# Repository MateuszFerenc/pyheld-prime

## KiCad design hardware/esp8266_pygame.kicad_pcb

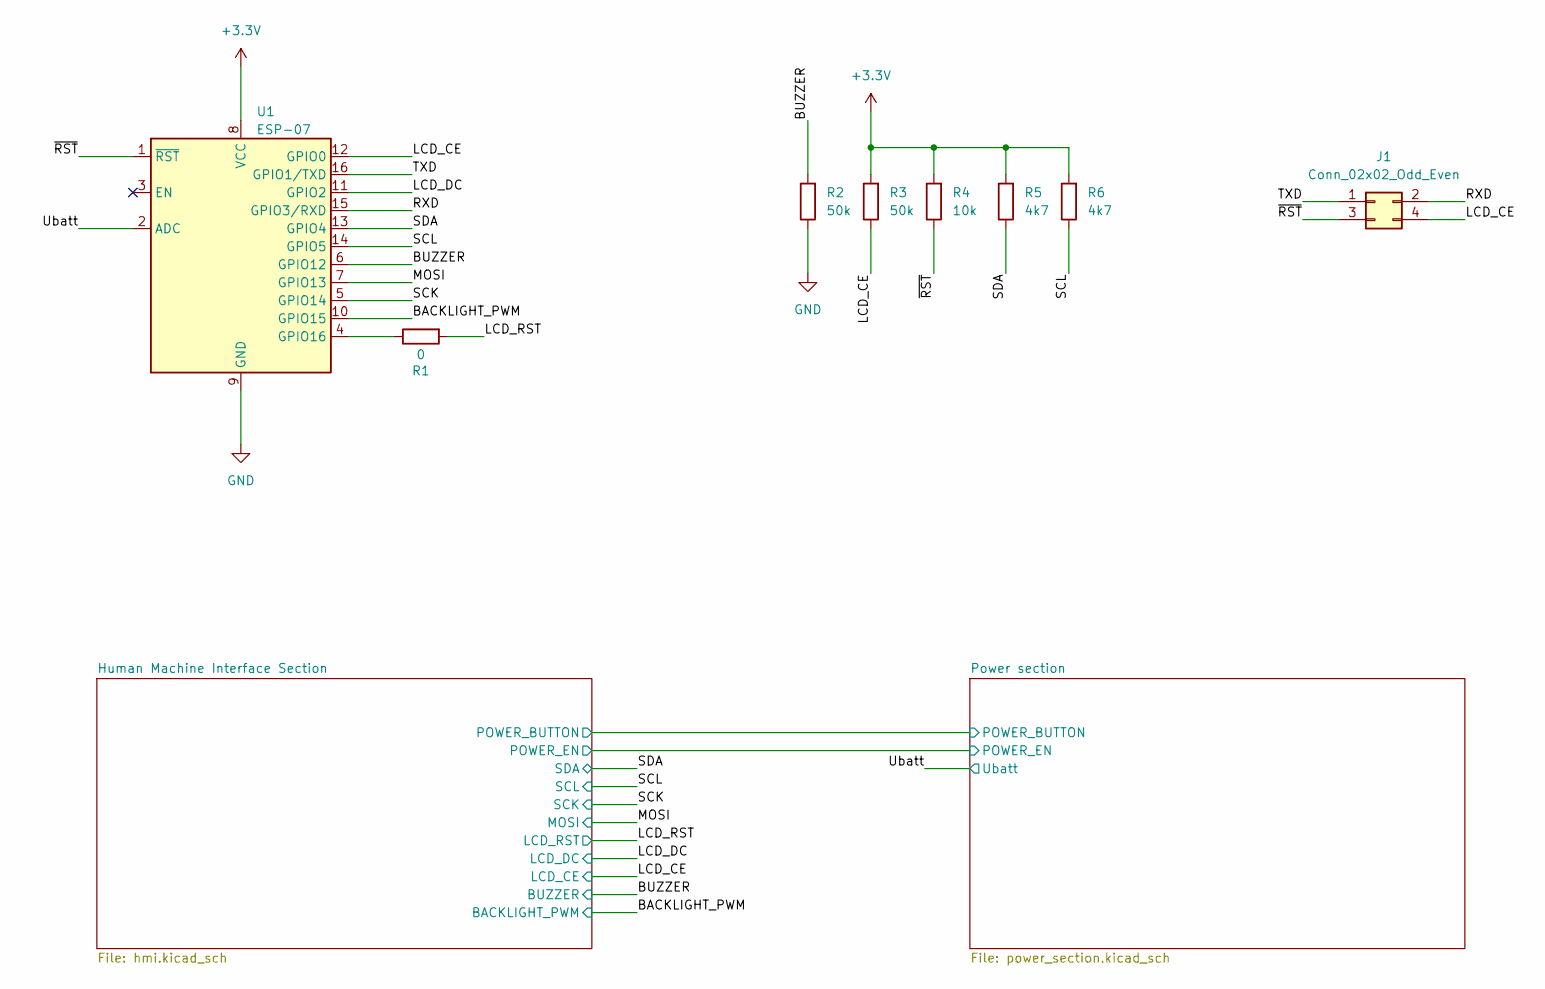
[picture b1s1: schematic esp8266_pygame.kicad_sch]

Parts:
J1: Conn_02x02_Odd_Even; PinHeader_2x02_P2.54mm_Vertical
R1: 0; R_0603_1608Metric
R2, R3: 50k; R_0603_1608Metric
R4: 10k; R_0603_1608Metric
R5, R6: 4k7; R_0603_1608Metric
U1: ESP-07

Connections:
+3.3V: R3.2, R4.2, R5.2, R6.2, U1.8 (VCC); also elsewhere on the board
/BACKLIGHT_PWM: U1.10 (GPIO15); also elsewhere on the board
/BUZZER: R2.2, U1.6 (GPIO12); also elsewhere on the board
/LCD_CE: J1.4, R3.1, U1.12 (GPIO0); also elsewhere on the board
/LCD_DC: U1.11 (GPIO2); also elsewhere on the board
/LCD_RST: R1.2; also elsewhere on the board
/MOSI: U1.7 (GPIO13); also elsewhere on the board
/RXD: J1.2, U1.15 (GPIO3/RXD)
/SCK: U1.5 (GPIO14); also elsewhere on the board
/SCL: R6.1, U1.14 (GPIO5); also elsewhere on the board
/SDA: R5.1, U1.13 (GPIO4); also elsewhere on the board
/TXD: J1.1, U1.16 (GPIO1/TXD)
/Ubatt: U1.2 (ADC); also elsewhere on the board
/~RST: J1.3, R4.1, U1.1 (~RST)
GND: R2.1, U1.9 (GND); also elsewhere on the board
unnamed: R1.1, U1.4 (GPIO16)

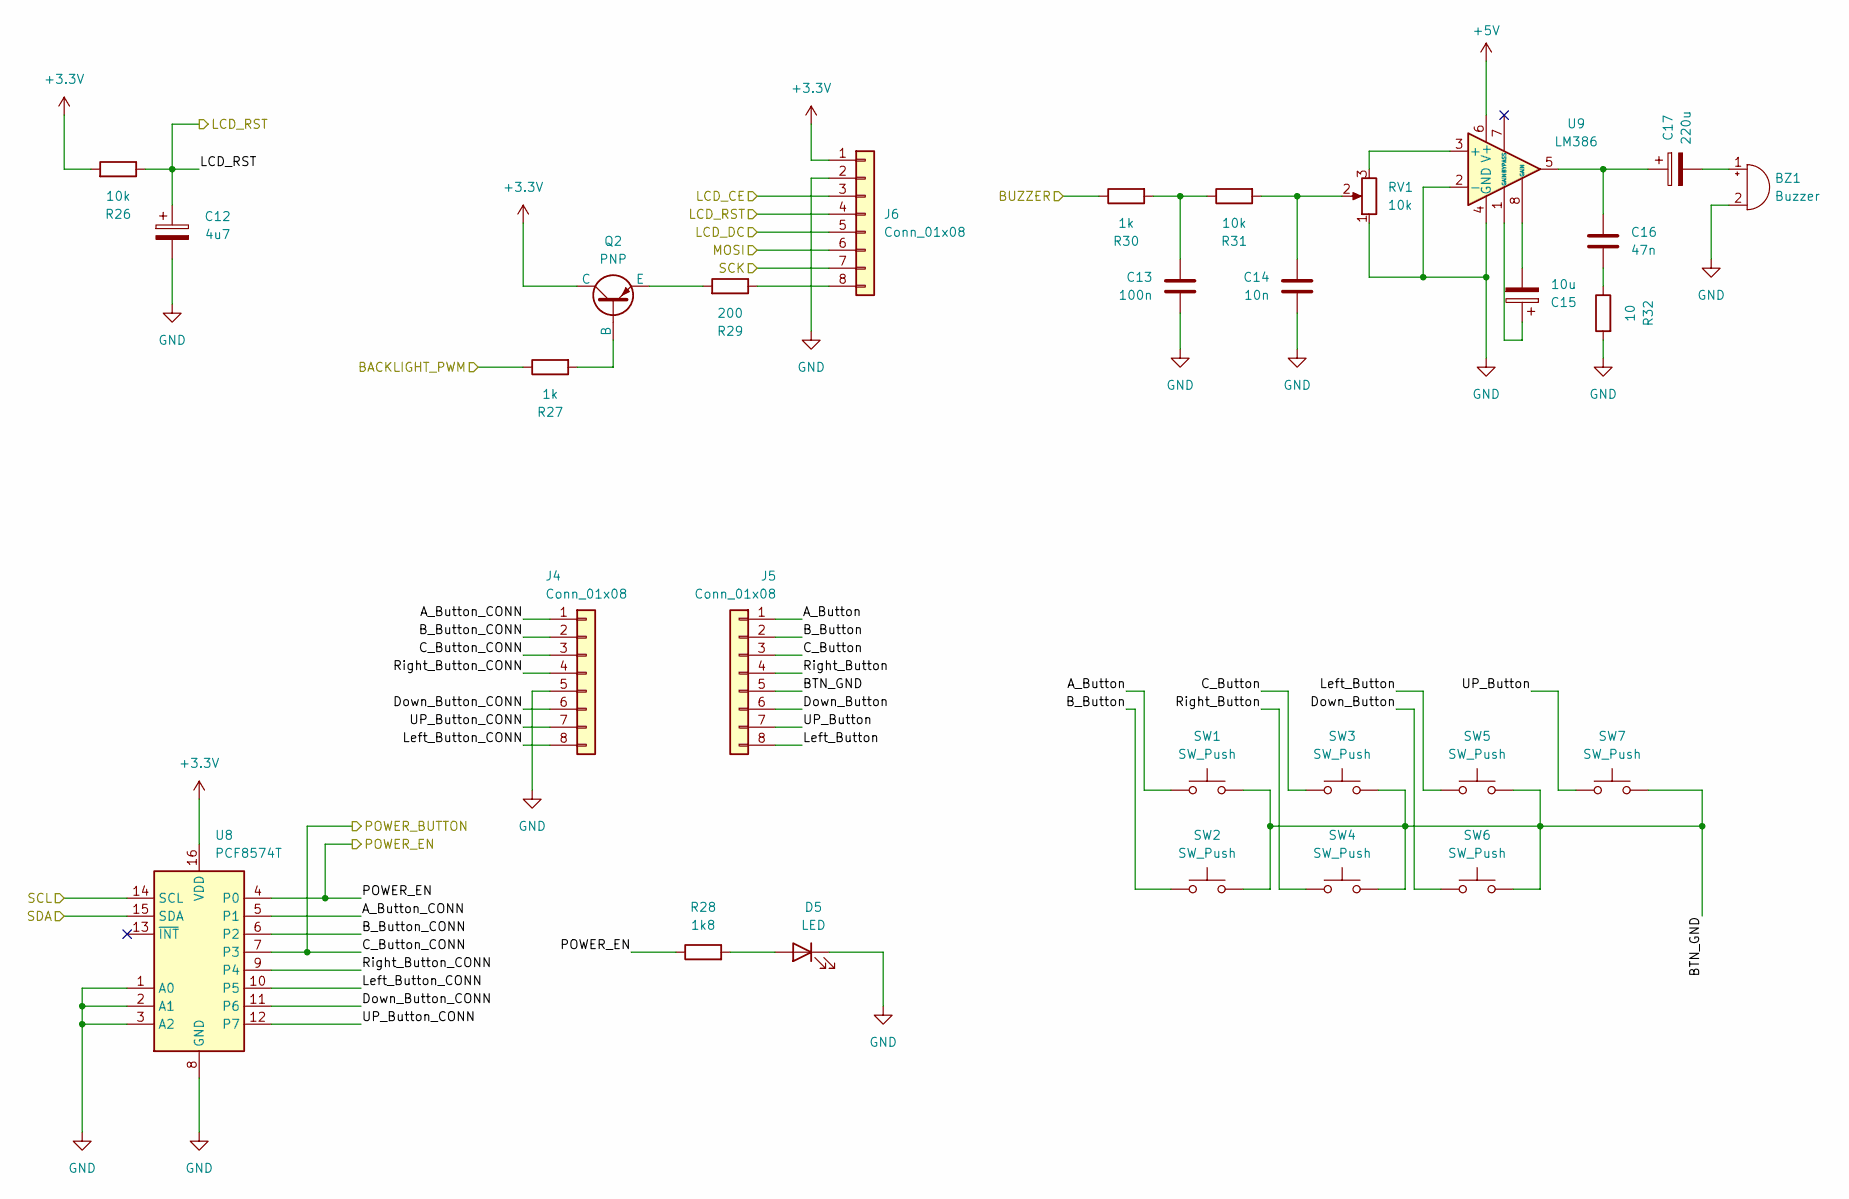
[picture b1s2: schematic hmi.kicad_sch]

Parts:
BZ1: Buzzer; PinHeader_1x02_P2.54mm_Vertical
C12: 4u7; CP_Radial_D4.0mm_P2.00mm
C13: 100n; C_0603_1608Metric
C14: 10n; C_0603_1608Metric
C15: 10u; CP_Radial_D4.0mm_P2.00mm
C16: 47n; C_0603_1608Metric
C17: 220u; CP_Radial_D4.0mm_P2.00mm
D5: LED; D_0603_1608Metric_Pad1.05x0.95mm_HandSolder
J4, J5: Conn_01x08; PinSocket_1x08_P2.54mm_Vertical
J6: Conn_01x08; PinHeader_1x08_P2.54mm_Vertical
Q2: PNP; SOT-23
R26, R31: 10k; R_0603_1608Metric
R27, R30: 1k; R_0603_1608Metric
R28: 1k8; R_0603_1608Metric
R29: 200; R_0603_1608Metric
R32: 10; R_0603_1608Metric
RV1: 10k; Potentiometer_Vishay_TS53YJ_Vertical
SW1, SW2, SW3, SW4, SW5, SW6, SW7: SW_Push; SW_SPST_TL3342
U8: PCF8574T; SOIC-16W_7.5x10.3mm_P1.27mm
U9: LM386; SO-8_3.9x4.9mm_P1.27mm

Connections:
+3.3V: J6.1, Q2.1 (C), R26.2, U8.16 (VDD); also elsewhere on the board
+5V: U9.6 (V+); also elsewhere on the board
/BACKLIGHT_PWM: R27.1; also elsewhere on the board
/BUZZER: R30.1; also elsewhere on the board
/Human Machine Interface Section/A_Button_CONN: J4.1, U8.5 (P1)
/Human Machine Interface Section/B_Button: J5.2, SW2.1
/Human Machine Interface Section/B_Button_CONN: J4.2, U8.6 (P2)
/Human Machine Interface Section/C_Button: J5.3, SW3.1
/Human Machine Interface Section/C_Button_CONN: J4.3, U8.7 (P3); also elsewhere on the board
/Human Machine Interface Section/Down_Button: J5.6, SW6.1
/Human Machine Interface Section/Down_Button_CONN: J4.6, U8.11 (P6)
/Human Machine Interface Section/Left_Button: J5.8, SW5.1
/Human Machine Interface Section/Left_Button_CONN: J4.8, U8.10 (P5)
/Human Machine Interface Section/POWER_EN: R28.1, U8.4 (P0); also elsewhere on the board
/Human Machine Interface Section/Right_Button: J5.4, SW4.1
/Human Machine Interface Section/Right_Button_CONN: J4.4, U8.9 (P4)
/Human Machine Interface Section/UP_Button: J5.7, SW7.1
/Human Machine Interface Section/UP_Button_CONN: J4.7, U8.12 (P7)
/LCD_CE: J6.3; also elsewhere on the board
/LCD_DC: J6.5; also elsewhere on the board
/LCD_RST: C12.1, J6.4, R26.1; also elsewhere on the board
/MOSI: J6.6; also elsewhere on the board
/SCK: J6.7; also elsewhere on the board
/SCL: U8.14 (SCL); also elsewhere on the board
/SDA: U8.15 (SDA); also elsewhere on the board
GND: BZ1.2 (+), C12.2, C13.1, C14.1, D5.1 (K), J4.5, J6.2, R32.2, RV1.1, U8.1 (A0), U8.2 (A1), U8.3 (A2), U8.8 (GND), U9.2 (-), U9.4 (GND); also elsewhere on the board
unnamed: BZ1.1 (-), C17.2
unnamed: C13.2, R30.2, R31.1
unnamed: C14.2, R31.2, RV1.2
unnamed: C15.1, U9.1 (GAIN)
unnamed: C15.2, U9.8 (GAIN)
unnamed: C16.1, R32.1
unnamed: C16.2, C17.1, U9.5
unnamed: D5.2 (A), R28.2
unnamed: J6.8, R29.1
unnamed: Q2.2 (B), R27.2
unnamed: Q2.3 (E), R29.2
unnamed: RV1.3, U9.3 (+)

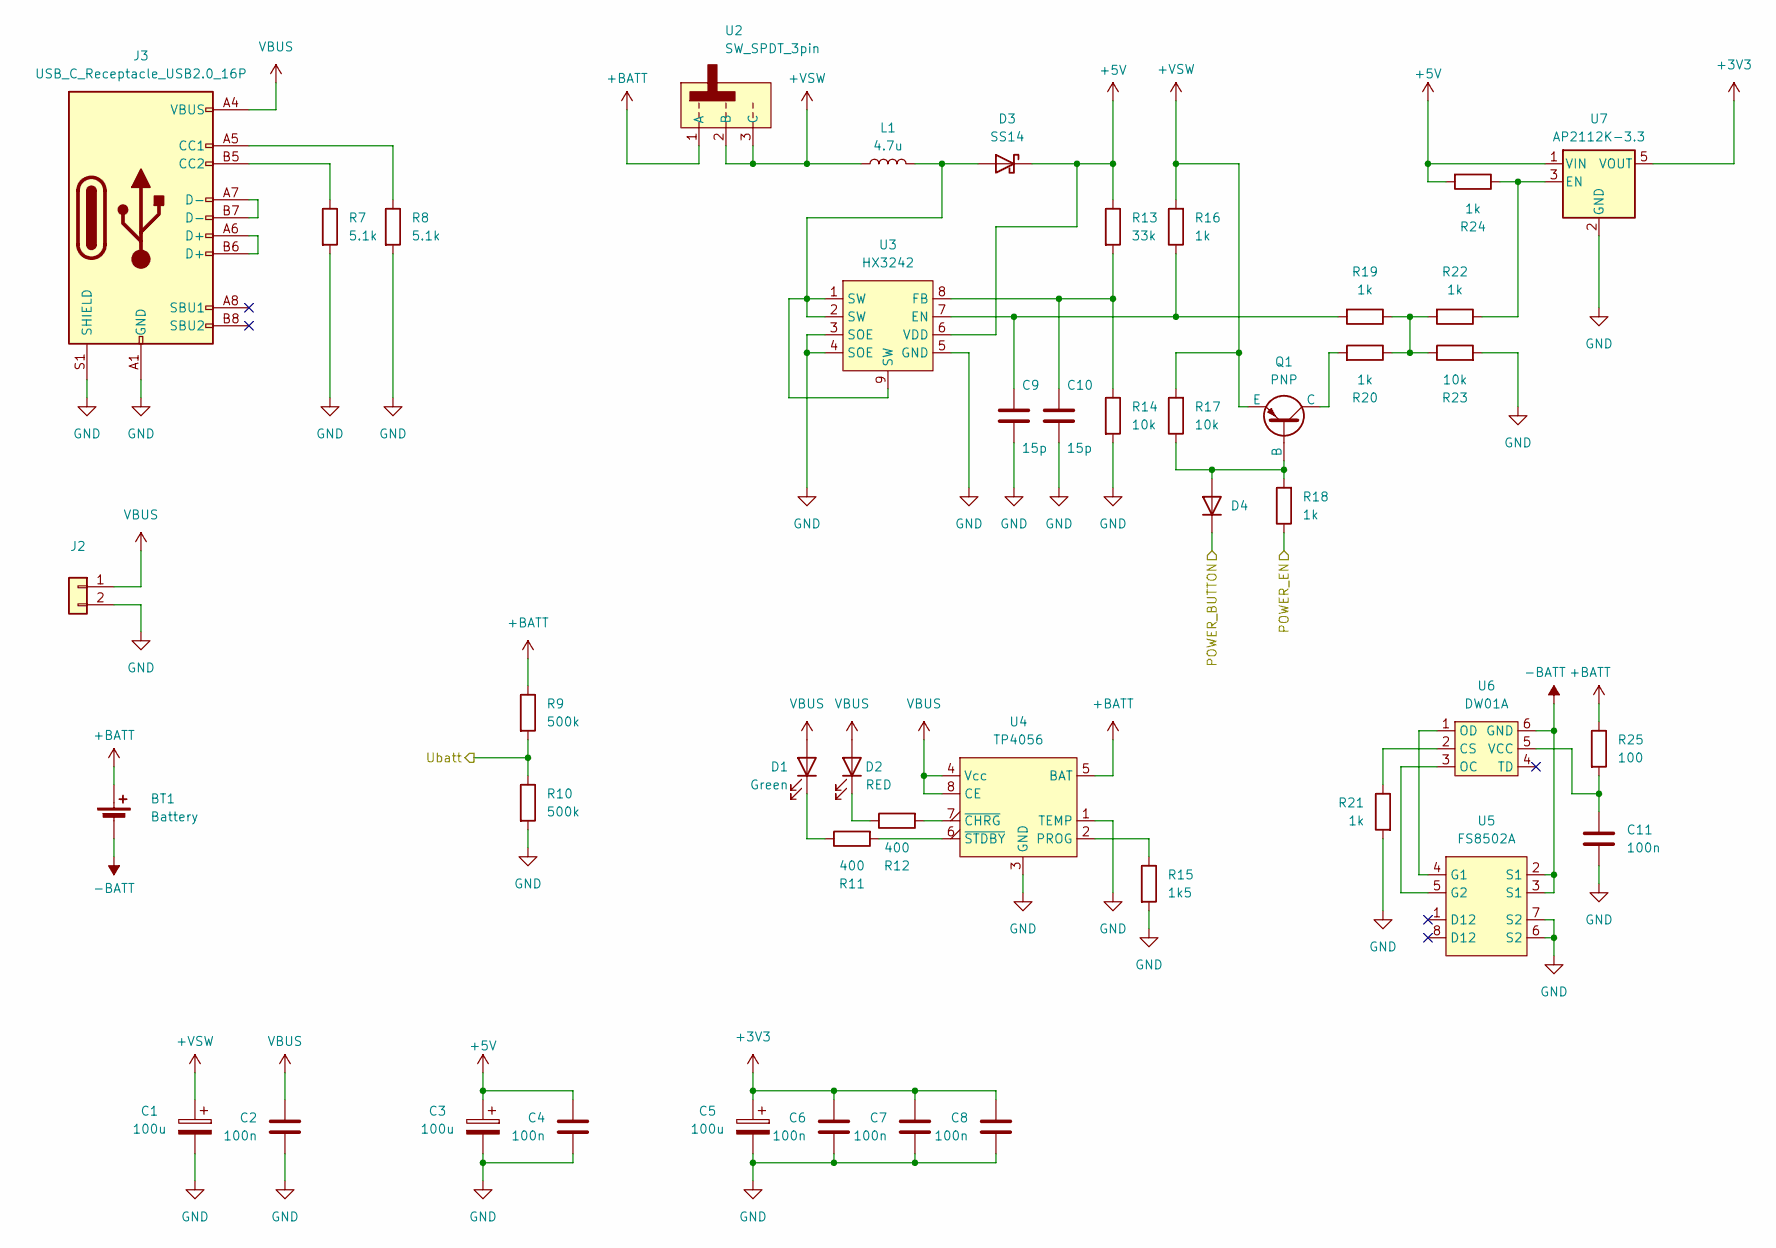
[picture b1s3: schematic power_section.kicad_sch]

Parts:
BT1: Battery; PinHeader_1x02_P2.54mm_Vertical
C1, C3, C5: 100u; CP_Elec_6.3x3
C2, C4, C6, C7, C8, C11: 100n; C_0603_1608Metric
C9, C10: 15p; C_0603_1608Metric
D1: Green; D_0603_1608Metric_Pad1.05x0.95mm_HandSolder
D2: RED; D_0603_1608Metric_Pad1.05x0.95mm_HandSolder
D3: SS14; D_SMA
D4: D; D_0805_2012Metric
J2: Conn_01x02; PinHeader_1x02_P2.54mm_Vertical
J3: USB_C_Receptacle_USB2.0_16P; USB_C_Receptacle_XKB_U262-16XN-4BVC11
L1: 4.7u; L_7.3x7.3_H3.5
Q1: PNP; SOT-23
R7, R8: 5.1k; R_0603_1608Metric
R9, R10: 500k; R_0603_1608Metric
R11, R12: 400; R_0603_1608Metric
R13: 33k; R_0805_2012Metric
R14: 10k; R_0805_2012Metric
R15: 1k5; R_0603_1608Metric
R16, R18, R19, R20, R21, R22, R24: 1k; R_0603_1608Metric
R17, R23: 10k; R_0603_1608Metric
R25: 100; R_0603_1608Metric
U2: SW_SPDT_3pin; my_switch
U3: HX3242; SOP-8-1EP_4.57x4.57mm_P1.27mm_EP4.57x4.45mm
U4: TP4056; SOIC-8-1EP_3.9x4.9mm_P1.27mm_EP2.29x3mm_ThermalVias
U5: FS8502A; TSSOP-8_4.4x3mm_P0.65mm
U6: DW01A; SOT-23-6
U7: AP2112K-3.3; SOT-23-5

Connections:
+3V3: C5.1, C6.2, C7.2, C8.2, U7.5 (VOUT)
+5V: C3.1, C4.2, D3.1 (K), R13.1, R24.2, U3.6 (VDD), U7.1 (VIN); also elsewhere on the board
+BATT: BT1.1 (+), R9.1, R25.1, U2.1 (A), U4.5 (BAT)
-BATT: BT1.2 (-), U5.2 (S1), U5.3 (S1), U6.6 (GND)
/Human Machine Interface Section/C_Button_CONN: D4.1 (K); also elsewhere on the board
/Human Machine Interface Section/POWER_EN: R18.1; also elsewhere on the board
/Ubatt: R9.2, R10.1; also elsewhere on the board
GND: C1.2, C2.1, C3.2, C4.1, C5.2, C6.1, C7.1, C8.1, C9.1, C10.1, C11.1, J2.2, J3.A1 (GND), J3.A12 (GND), J3.B1 (GND), J3.B12 (GND), J3.S1 (SHIELD), R7.2, R8.2, R10.2, R14.2, R15.2, R21.2, R23.2, U3.3 (SOE), U3.4 (SOE), U3.5 (GND), U4.1 (TEMP), U4.3 (GND), U4.9 (GND), U5.6 (S2), U5.7 (S2), U7.2 (GND); also elsewhere on the board
unnamed: D1.1 (K), R11.1
unnamed: D2.1 (K), R12.1
unnamed: D3.2 (A), L1.2, U3.1 (SW), U3.2 (SW), U3.9 (SW)
unnamed: D4.2 (A), Q1.2 (B), R17.1, R18.2
unnamed: J3.A5 (CC1), R8.1
unnamed: J3.B5 (CC2), R7.1
unnamed: J3.A6 (D+), J3.B6 (D+)
unnamed: J3.A7 (D-), J3.B7 (D-)
unnamed: Q1.1 (C), R20.2
unnamed: R19.1, R20.1, R22.2, R23.1
unnamed: C9.2, R16.1, R19.2, U3.7 (EN)
unnamed: C10.2, R13.2, R14.1, U3.8 (FB)
unnamed: R15.1, U4.2 (PROG)
unnamed: R12.2, U4.7 (~CHRG)
unnamed: R11.2, U4.6 (~STDBY)
unnamed: U5.4 (G1), U6.1 (OD)
unnamed: U5.5 (G2), U6.3 (OC)
unnamed: R21.1, U6.2 (CS)
unnamed: C11.2, R25.2, U6.5 (VCC)
unnamed: R22.1, R24.1, U7.3 (EN)
VBUS: C2.2, D1.2 (A), D2.2 (A), J2.1, J3.A4 (VBUS), J3.A9 (VBUS), J3.B4 (VBUS), J3.B9 (VBUS), U4.4 (Vcc), U4.8 (CE)

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
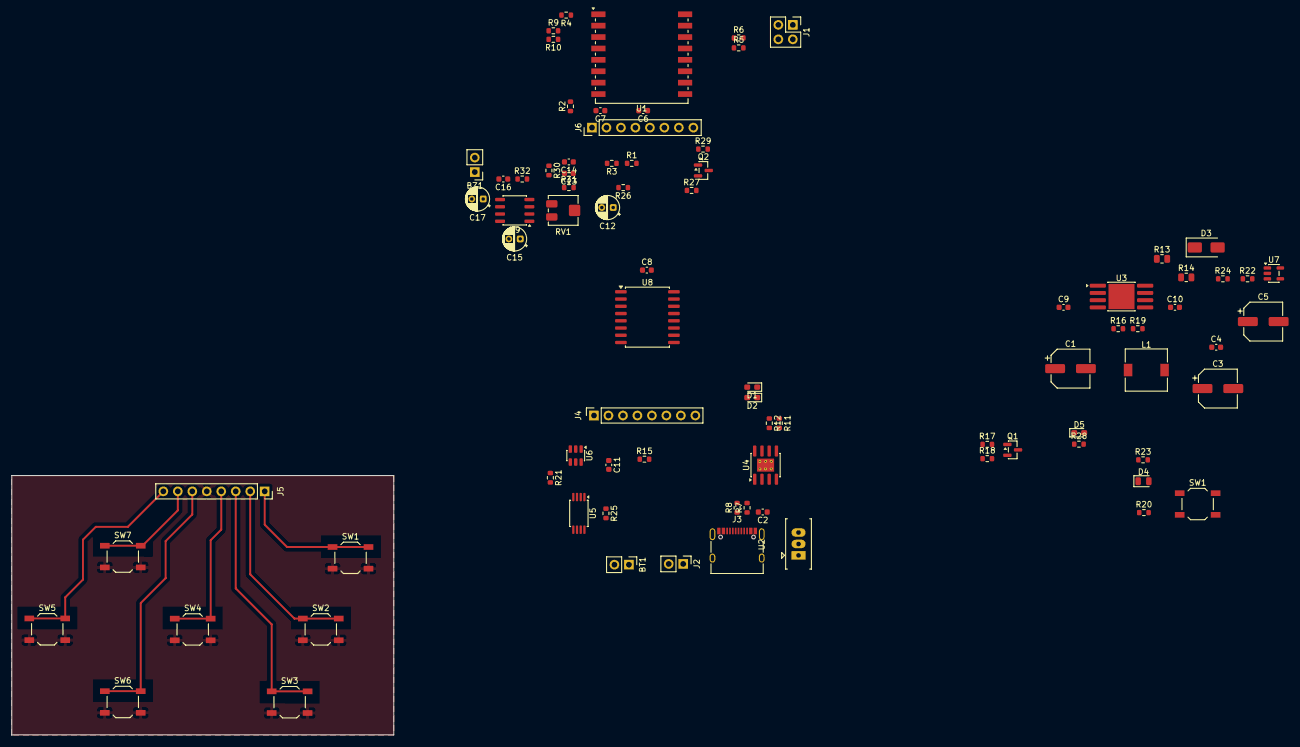
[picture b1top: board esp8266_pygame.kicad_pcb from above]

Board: 2 copper layers, 67.0 x 45.5 mm, 83 parts (0 on the bottom side), 70 nets.

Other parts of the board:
SW1#2: SW_Push; SW_SPST_TL3342

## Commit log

2026-01-13 initial commit - first project files
2026-01-13 Added display rotation
2026-01-14 fixed hardware, proxu not needed
2026-01-15 Fixed game loading and buttons
2026-01-15 Working game flappy v1.0
2026-01-15 Game flappy all working, added startup logo
2026-01-15 Snake game added
2026-01-16 Added button combo callbacks and multiline text
2026-01-16 Minor changes
    Scripts are deployed as python binary now (using deploy.py)
    Games names are dynamically loaded from the file system, not statically as before
2026-01-16 Snake game adjusted logic to elliptical snake and apple
2026-01-16 Fixed snake food generation, added pacman template
2026-01-16 Optimization: wifi disabled
2026-01-20 Fixed list of available apps Some minor changes.
    main.py:
    - added version to logo (on startup)
    - added scroll to application list, now list of available apps is dynamically generated and scrolled (on key press)
    logo.pbm:
    - project changed name from "pyheld" to "pyheld - prime" because it's first prototype of original idea
    hardware.py:
2026-01-21 Unstable - WiP
2026-01-25 Slight performance iprovements
2026-01-25 added schematic
2026-01-27 Refactor game display text and improve system info output
2026-01-28 Refactor imports and improve game loading error handling; add new PBM asset for Stack Attack
2026-02-02 Fixed logic in games and added pong game
2026-02-03 Minor changes - pong logic, deploy and hardware
    pong.py
    - fixed movements of the paddles
    hardware.py
    - class ButtonEvents - added method to return true if button is currently pressed
    deploy.py
    - added optimization flag, to load only updated files (faster files update)
2026-02-19 New PCB schematic ready
2026-02-19 Second revision of schematic
2026-02-20 Initial PCB placement and some schematic changes
2026-02-26 Fixed keypad connector
2026-03-02 Audio improvements
2026-03-04 Fixed power enable bypass
2026-04-03 Add PCB edges marks
